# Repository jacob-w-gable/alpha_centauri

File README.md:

# Alpha Centauri KBD

This is a custom keyboard with a custom keymap that is specifically tailored to my hands and workflow style. It takes heavy inspiration from [crkbd v3](https://github.com/foostan/crkbd). The primary difference is the vertical spacing of the keys, and I have also removed one key from the outside column. The PCB is designed to support either MX or Choc v2 switches without sacrificing LED support. The keymap has been designed for comfort and efficiency, prioritizing typing/programming over other activities such as gaming.

### Assembled Choc Keyboard

### Assembled MX Keyboard

## Detailed Documentation

- [Quickstart](https://github.com/jacob-w-gable/alpha_centauri/wiki/Quickstart)
- [Designing/Fabricating the PCB](https://github.com/jacob-w-gable/alpha_centauri/wiki/Designing-and-Fabricating-PCB)
- TODO: PCB Assembly
- [Building/Flashing the Firmware](https://github.com/jacob-w-gable/alpha_centauri/wiki/Building-and-Flashing-Firmware)
- TODO: Printing the Case
- TODO: Final Assembly
- [Technical Layer Reference](https://github.com/jacob-w-gable/alpha_centauri/wiki/Technical-Layer-Reference)
- [Design Philosophy](https://github.com/jacob-w-gable/alpha_centauri/wiki/Design)

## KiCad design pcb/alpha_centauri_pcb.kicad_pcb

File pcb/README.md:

# PCB Files

These are the files required to edit the PCB in Kicad. One thing that makes this PCB stand out, is the fact that you can use hotswap sockets for either MX or Choc style switches, without compromising the ability to use per-key LEDs. While this does unfortunately cut off one of the pads, it does not make an electrical difference.

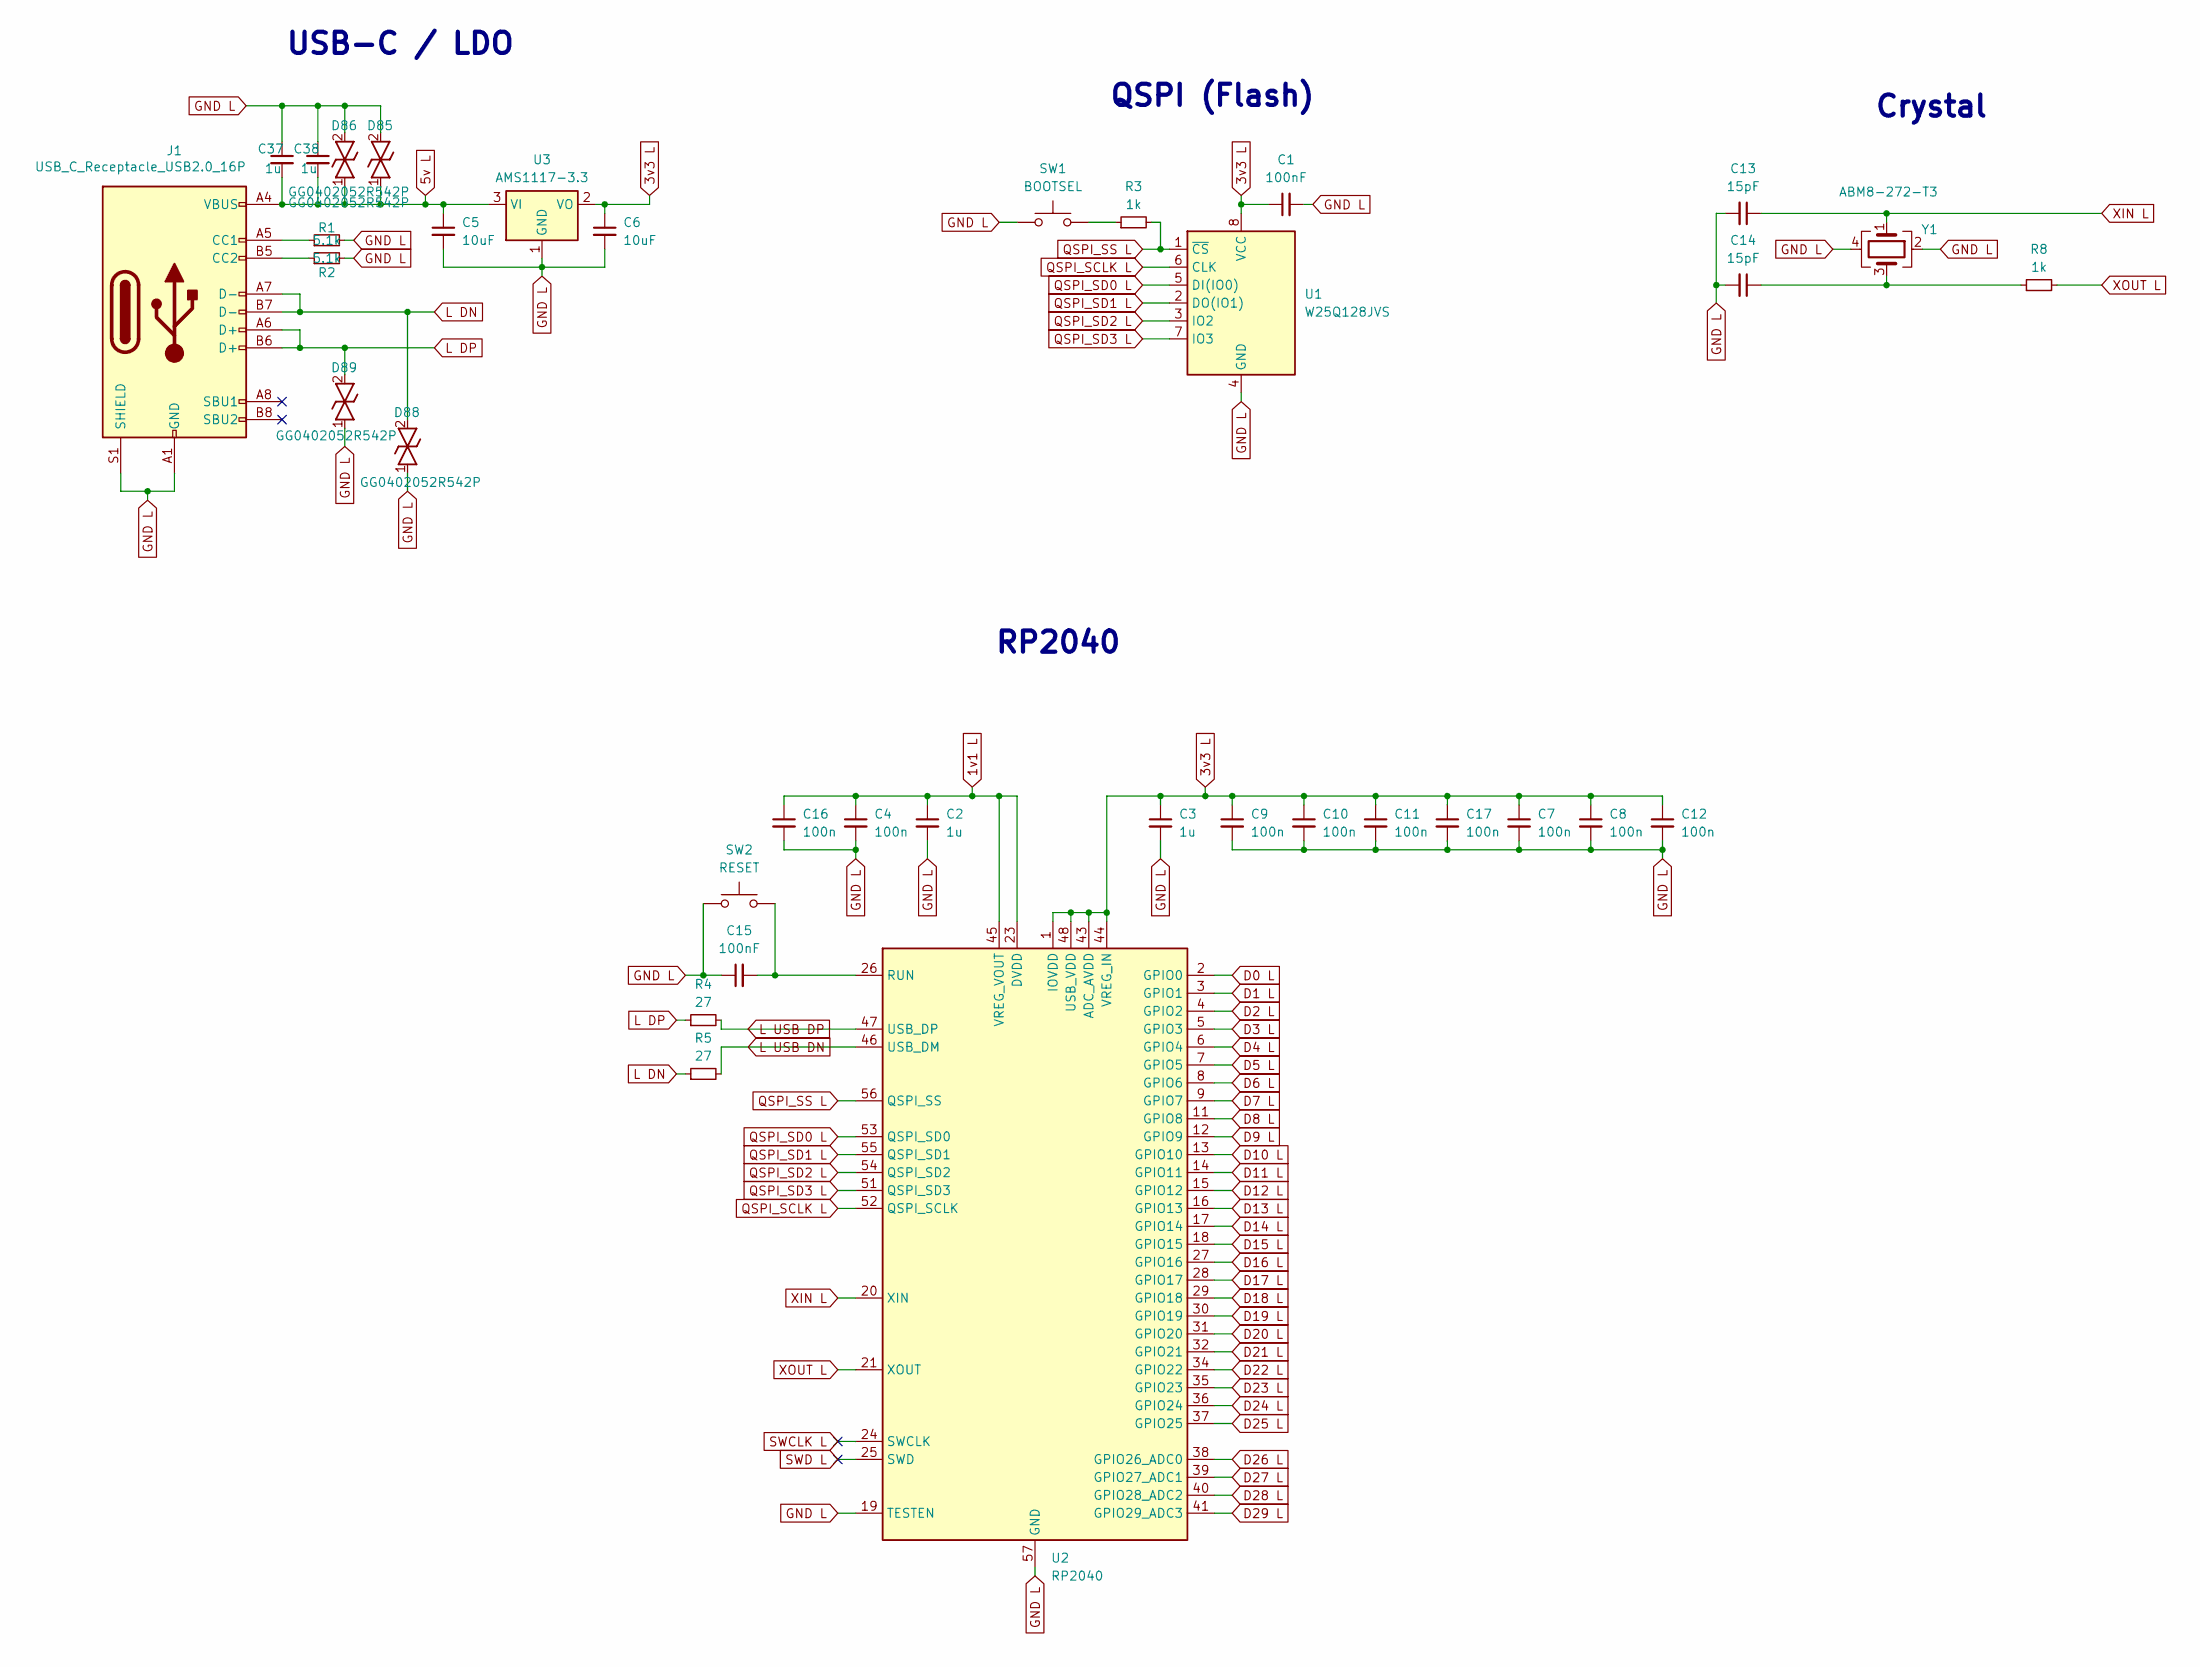
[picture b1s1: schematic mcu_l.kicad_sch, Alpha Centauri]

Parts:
C1, C15: 100nF; C_0603_1608Metric
C2, C3, C37, C38: 1u; C_0603_1608Metric
C4, C7, C8, C9, C10, C11, C12, C16, C17: 100n; C_0603_1608Metric
C5, C6: 10uF; C_0805_2012Metric
C13, C14: 15pF; C_0603_1608Metric
D85, D86, D88, D89: GG0402052R542P; DIONC1006X55N; Manufacturer_Part_Number GG0402052R542P; Mouser Part Number 581-GG0402052R542P
J1: USB_C_Receptacle_USB2.0_16P; USB_C_Receptacle_HRO_TYPE-C-31-M-12
R1, R2: 5.1k; R_0603_1608Metric
R3, R8: 1k; R_0603_1608Metric
R4, R5: 27; R_0603_1608Metric
SW1: BOOTSEL; EVQP2202M
SW2: RESET; EVQP2202M
U1: W25Q128JVS; SOIC127P790X216-8N
U2: RP2040; QFN-56-1EP_7x7mm_P0.4mm_EP3.2x3.2mm
U3: AMS1117-3.3; SOT-223-3_TabPin2
Y1: ABM8-272-T3; Crystal_SMD_3225-4Pin_3.2x2.5mm

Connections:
1v1 L: C2.1, C4.1, C16.1, U2.23 (DVDD), U2.45 (VREG_VOUT), U2.50 (DVDD)
3v3 L: C1.1, C3.1, C6.1, C7.1, C8.1, C9.1, C10.1, C11.1, C12.1, C17.1, U1.8 (VCC), U2.1 (IOVDD), U2.10 (IOVDD), U2.22 (IOVDD), U2.33 (IOVDD), U2.42 (IOVDD), U2.43 (ADC_AVDD), U2.44 (VREG_IN), U2.48 (USB_VDD), U2.49 (IOVDD), U3.2 (VO)
5v L: C5.1, C37.2, C38.2, D85.1, D86.1, J1.A4 (VBUS), J1.A9 (VBUS), J1.B4 (VBUS), J1.B9 (VBUS), U3.3 (VI); also elsewhere on the board
D0 L: U2.2 (GPIO0); also elsewhere on the board
D1 L: U2.3 (GPIO1)
D2 L: U2.4 (GPIO2)
D3 L: U2.5 (GPIO3)
D4 L: U2.6 (GPIO4); also elsewhere on the board
D5 L: U2.7 (GPIO5); also elsewhere on the board
D6 L: U2.8 (GPIO6); also elsewhere on the board
D7 L: U2.9 (GPIO7); also elsewhere on the board
D8 L: U2.11 (GPIO8); also elsewhere on the board
D9 L: U2.12 (GPIO9); also elsewhere on the board
D10 L: U2.13 (GPIO10)
D11 L: U2.14 (GPIO11)
D12 L: U2.15 (GPIO12)
D13 L: U2.16 (GPIO13)
D14 L: U2.17 (GPIO14)
D15 L: U2.18 (GPIO15)
D16 L: U2.27 (GPIO16)
D17 L: U2.28 (GPIO17)
D18 L: U2.29 (GPIO18)
D19 L: U2.30 (GPIO19)
D20 L: U2.31 (GPIO20); also elsewhere on the board
D21 L: U2.32 (GPIO21)
D22 L: U2.34 (GPIO22); also elsewhere on the board
D23 L: U2.35 (GPIO23)
D24 L: U2.36 (GPIO24)
D25 L: U2.37 (GPIO25)
D26 L: U2.38 (GPIO26_ADC0); also elsewhere on the board
D27 L: U2.39 (GPIO27_ADC1); also elsewhere on the board
D28 L: U2.40 (GPIO28_ADC2); also elsewhere on the board
D29 L: U2.41 (GPIO29_ADC3); also elsewhere on the board
GND L: C1.2, C2.2, C3.2, C4.2, C5.2, C6.2, C7.2, C8.2, C9.2, C10.2, C11.2, C12.2, C13.2, C14.2, C15.1, C16.2, C17.2, C37.1, C38.1, D85.2, D86.2, D88.1, D89.1, J1.A1 (GND), J1.A12 (GND), J1.B1 (GND), J1.B12 (GND), J1.S1 (SHIELD), R1.2, R2.2, SW1.1, SW2.1, U1.4 (GND), U2.19 (TESTEN), U2.57 (GND), U3.1 (GND), Y1.2, Y1.4; also elsewhere on the board
L DN: D88.2, J1.A7 (D-), J1.B7 (D-), R5.1
L DP: D89.2, J1.A6 (D+), J1.B6 (D+), R4.1
L USB DN: R5.2, U2.46 (USB_DM)
L USB DP: R4.2, U2.47 (USB_DP)
unnamed: C14.1, R8.1, Y1.3
unnamed: J1.A5 (CC1), R1.1
unnamed: J1.B5 (CC2), R2.1
unnamed: R3.1, SW1.2
unnamed: C15.2, SW2.2, U2.26 (RUN)
QSPI_SCLK L: U1.6 (CLK), U2.52 (QSPI_SCLK)
QSPI_SD0 L: U1.5 (DI(IO0)), U2.53 (QSPI_SD0)
QSPI_SD1 L: U1.2 (DO(IO1)), U2.55 (QSPI_SD1)
QSPI_SD2 L: U1.3 (IO2), U2.54 (QSPI_SD2)
QSPI_SD3 L: U1.7 (IO3), U2.51 (QSPI_SD3)
QSPI_SS L: R3.2, U1.1 (~CS), U2.56 (QSPI_SS)
SWCLK L: U2.24 (SWCLK)
SWD L: U2.25 (SWD)
XIN L: C13.1, U2.20 (XIN), Y1.1
XOUT L: R8.2, U2.21 (XOUT)

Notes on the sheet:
RP2040
QSPI (Flash)
USB-C / LDO
Crystal

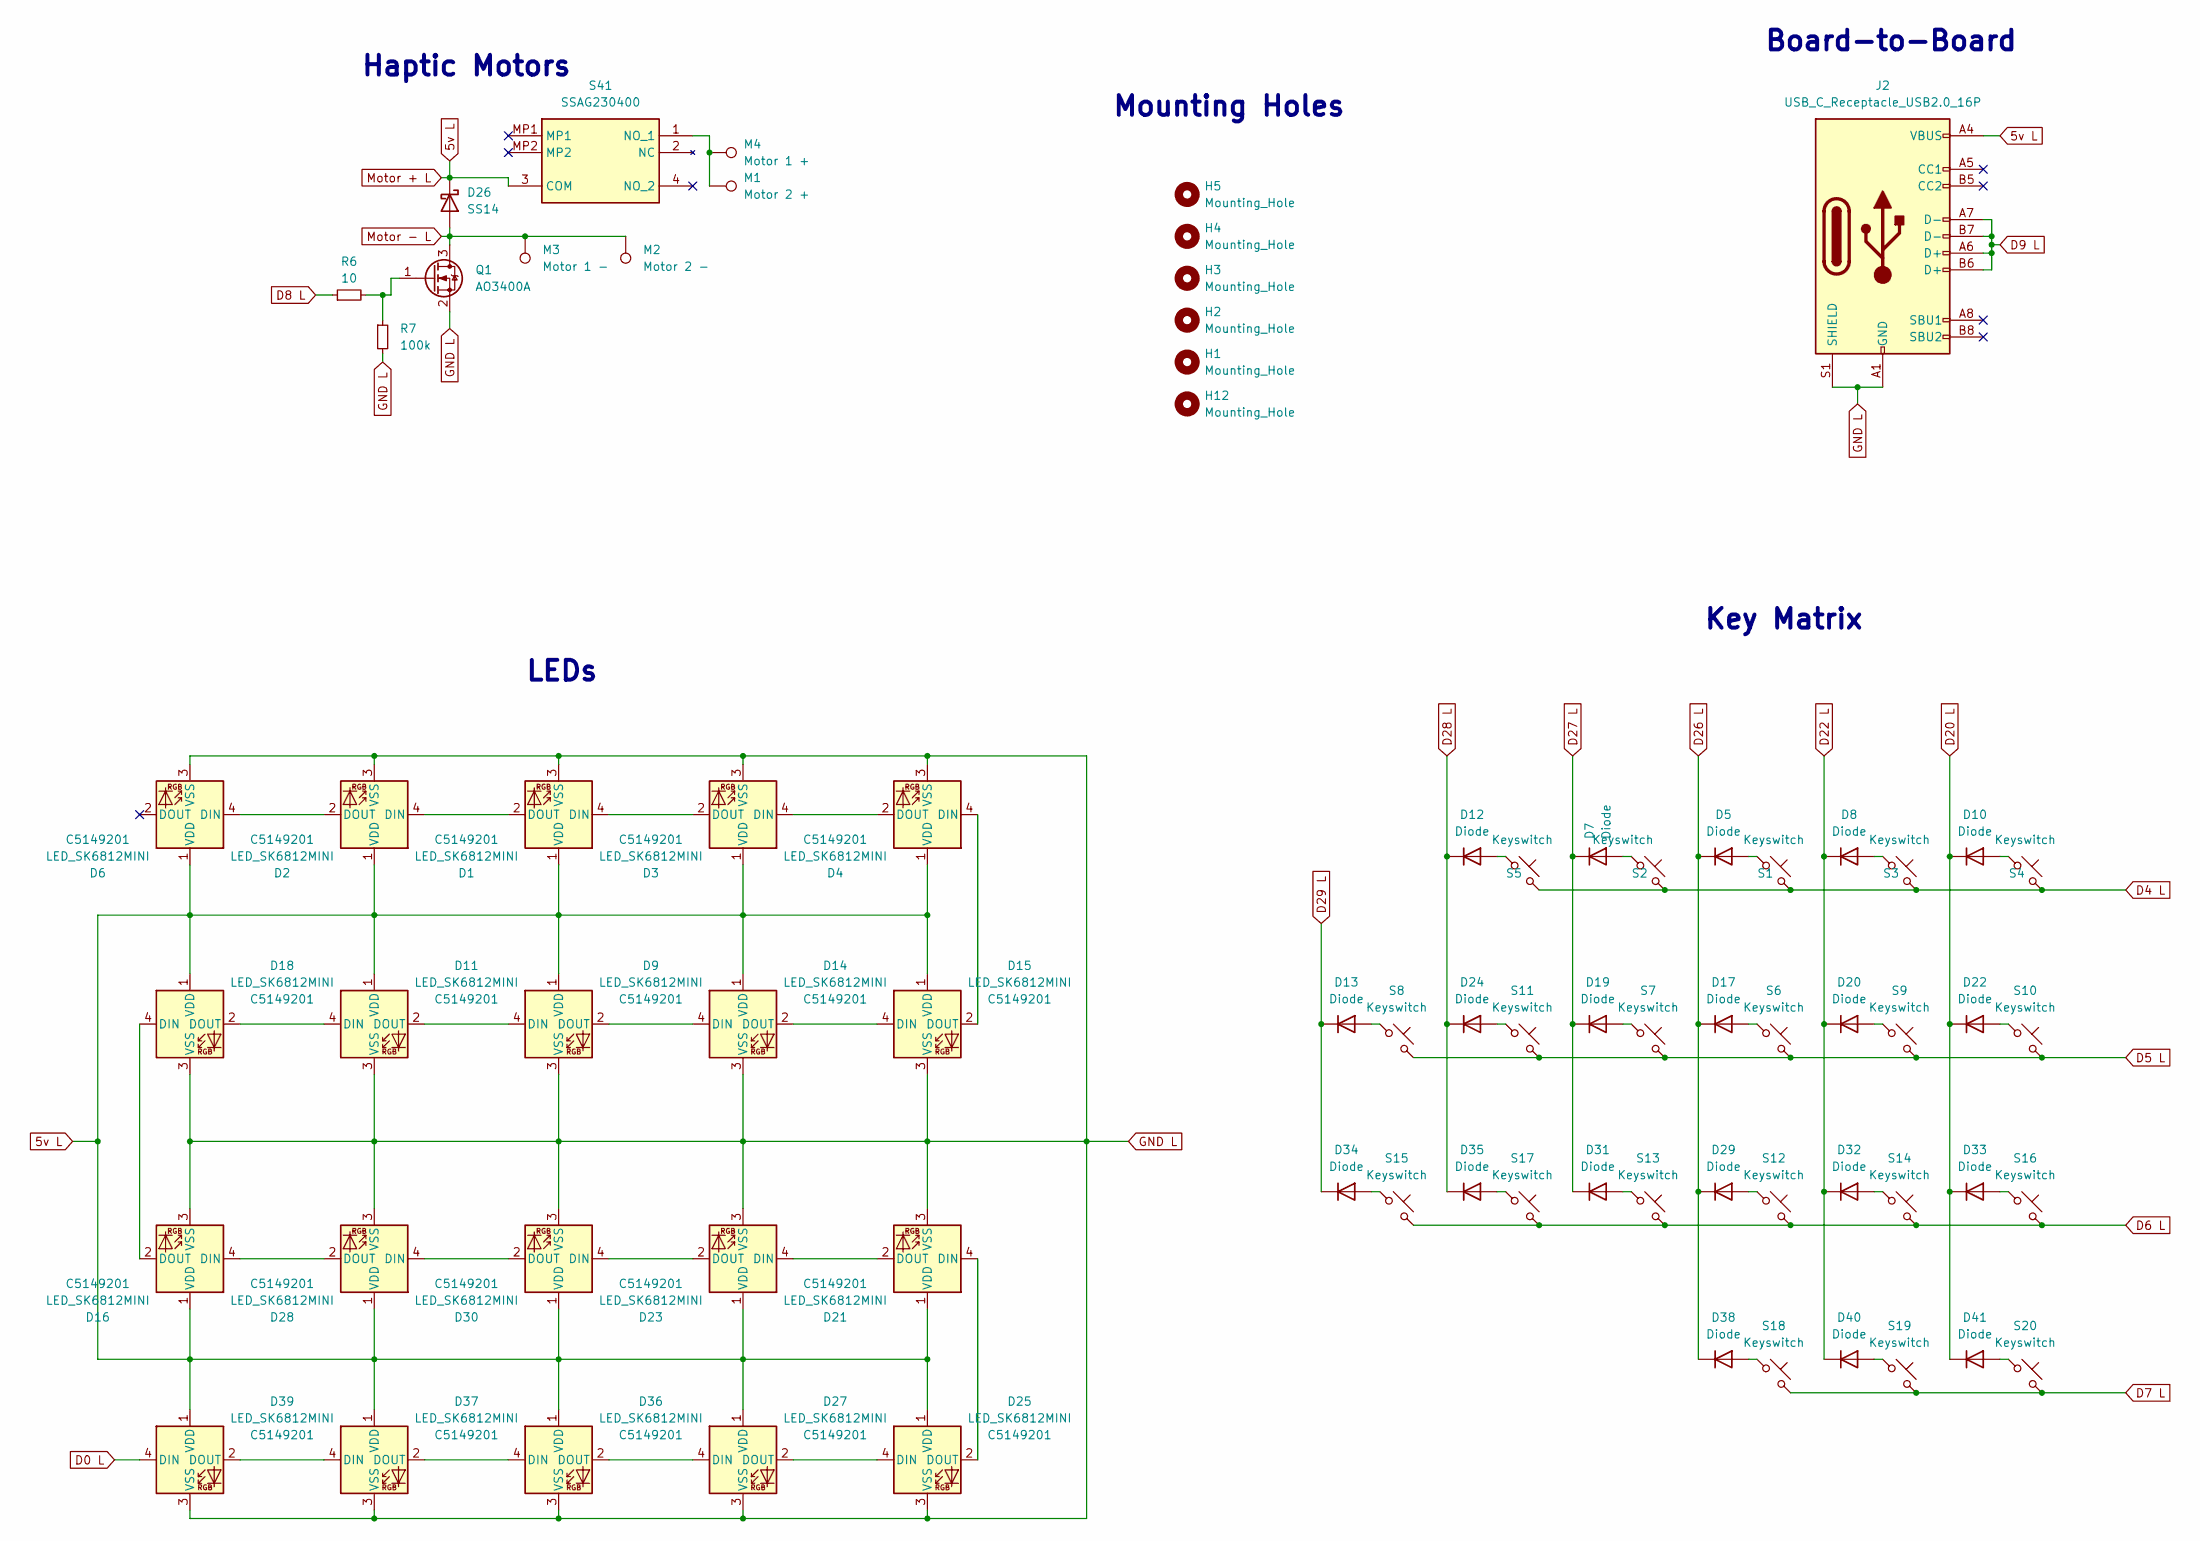
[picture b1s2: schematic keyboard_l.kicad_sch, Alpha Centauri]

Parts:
D1, D2, D3, D4, D6, D9, D11, D14, D15, D16, D18, D21, D23, D25, D27, D28, D30, D36, D37, D39: LED_SK6812MINI; LCSC C5149201
D5, D7, D8, D10, D12, D13, D17, D19, D20, D22, D24, D29, D31, D32, D33, D34, D35, D38, D40, D41: Diode; Diode_SOD-123
D26: SS14; D_SMA
H1, H2, H3, H4, H5, H12: Mounting_Hole; MountingHole_4.3mm_M4
J2: USB_C_Receptacle_USB2.0_16P; USB_C_Receptacle_HRO_TYPE-C-31-M-12
M1: Motor 2 +; TestPoint_Pad_2.5x2.5mm
M2: Motor 2 -; TestPoint_Pad_2.5x2.5mm
M3: Motor 1 -; TestPoint_Pad_2.5x2.5mm
M4: Motor 1 +; TestPoint_Pad_2.5x2.5mm
Q1: AO3400A; SOT-23
R6: 10; R_0603_1608Metric
R7: 100k; R_0603_1608Metric
S1, S2, S3, S4, S5, S6, S7, S9, S10, S11, S12, S13, S14, S15, S16, S17, S18, S19, S20: Keyswitch; MX_Choc_Hotswap_Hybrid
S8: Keyswitch; MX_Choc_Hotswap_Hybrid_1.5u
S41: SSAG230400; Manufacturer_Part_Number SSAG230400; Mouser Part Number 688-SSAG230400

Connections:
5v L: D1.1 (VDD), D2.1 (VDD), D3.1 (VDD), D4.1 (VDD), D6.1 (VDD), D9.1 (VDD), D11.1 (VDD), D14.1 (VDD), D15.1 (VDD), D16.1 (VDD), D18.1 (VDD), D21.1 (VDD), D23.1 (VDD), D25.1 (VDD), D26.1 (K), D27.1 (VDD), D28.1 (VDD), D30.1 (VDD), D36.1 (VDD), D37.1 (VDD), D39.1 (VDD), J2.A4 (VBUS), J2.A9 (VBUS), J2.B4 (VBUS), J2.B9 (VBUS), S41.3 (COM); also elsewhere on the board
D0 L: D39.4 (DIN); also elsewhere on the board
D4 L: S1.2, S2.2, S3.2, S4.2, S5.2; also elsewhere on the board
D5 L: S6.2, S7.2, S8.2, S9.2, S10.2, S11.2; also elsewhere on the board
D6 L: S12.2, S13.2, S14.2, S15.2, S16.2, S17.2; also elsewhere on the board
D7 L: S18.2, S19.2, S20.2; also elsewhere on the board
D8 L: R6.1; also elsewhere on the board
D9 L: J2.A6 (D+), J2.A7 (D-), J2.B6 (D+), J2.B7 (D-); also elsewhere on the board
D20 L: D10.1 (K), D22.1 (K), D33.1 (K), D41.1 (K); also elsewhere on the board
D22 L: D8.1 (K), D20.1 (K), D32.1 (K), D40.1 (K); also elsewhere on the board
D26 L: D5.1 (K), D17.1 (K), D29.1 (K), D38.1 (K); also elsewhere on the board
D27 L: D7.1 (K), D19.1 (K), D31.1 (K); also elsewhere on the board
D28 L: D12.1 (K), D24.1 (K), D35.1 (K); also elsewhere on the board
D29 L: D13.1 (K), D34.1 (K); also elsewhere on the board
GND L: D1.3 (VSS), D2.3 (VSS), D3.3 (VSS), D4.3 (VSS), D6.3 (VSS), D9.3 (VSS), D11.3 (VSS), D14.3 (VSS), D15.3 (VSS), D16.3 (VSS), D18.3 (VSS), D21.3 (VSS), D23.3 (VSS), D25.3 (VSS), D27.3 (VSS), D28.3 (VSS), D30.3 (VSS), D36.3 (VSS), D37.3 (VSS), D39.3 (VSS), J2.A1 (GND), J2.A12 (GND), J2.B1 (GND), J2.B12 (GND), J2.S1 (SHIELD), Q1.2 (S), R7.2; also elsewhere on the board
Motor - L: D26.2 (A), M2.1 (1_1), M3.1 (1_1), Q1.3 (D)
unnamed: D1.4 (DIN), D3.2 (DOUT)
unnamed: D1.2 (DOUT), D2.4 (DIN)
unnamed: D2.2 (DOUT), D6.4 (DIN)
unnamed: D3.4 (DIN), D4.2 (DOUT)
unnamed: D5.2 (A), S1.1
unnamed: D7.2 (A), S2.1
unnamed: D8.2 (A), S3.1
unnamed: D10.2 (A), S4.1
unnamed: D11.4 (DIN), D18.2 (DOUT)
unnamed: D9.4 (DIN), D11.2 (DOUT)
unnamed: D12.2 (A), S5.1
unnamed: D13.2 (A), S8.1
unnamed: D9.2 (DOUT), D14.4 (DIN)
unnamed: D14.2 (DOUT), D15.4 (DIN)
unnamed: D4.4 (DIN), D15.2 (DOUT)
unnamed: D16.4 (DIN), D28.2 (DOUT)
unnamed: D16.2 (DOUT), D18.4 (DIN)
unnamed: D17.2 (A), S6.1
unnamed: D19.2 (A), S7.1
unnamed: D20.2 (A), S9.1
unnamed: D21.4 (DIN), D25.2 (DOUT)
unnamed: D21.2 (DOUT), D23.4 (DIN)
unnamed: D22.2 (A), S10.1
unnamed: D23.2 (DOUT), D30.4 (DIN)
unnamed: D24.2 (A), S11.1
unnamed: D25.4 (DIN), D27.2 (DOUT)
unnamed: D27.4 (DIN), D36.2 (DOUT)
unnamed: D28.4 (DIN), D30.2 (DOUT)
unnamed: D29.2 (A), S12.1
unnamed: D31.2 (A), S13.1
unnamed: D32.2 (A), S14.1
unnamed: D33.2 (A), S16.1
unnamed: D34.2 (A), S15.1
unnamed: D35.2 (A), S17.1
unnamed: D36.4 (DIN), D37.2 (DOUT)
unnamed: D37.4 (DIN), D39.2 (DOUT)
unnamed: D38.2 (A), S18.1
unnamed: D40.2 (A), S19.1
unnamed: D41.2 (A), S20.1
unnamed: Q1.1 (G), R6.2, R7.1
unnamed: M1.1 (1_1), M4.1 (1_1), S41.1 (NO_1)

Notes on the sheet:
Board-to-Board
Haptic Motors
Key Matrix
LEDs
Mounting Holes

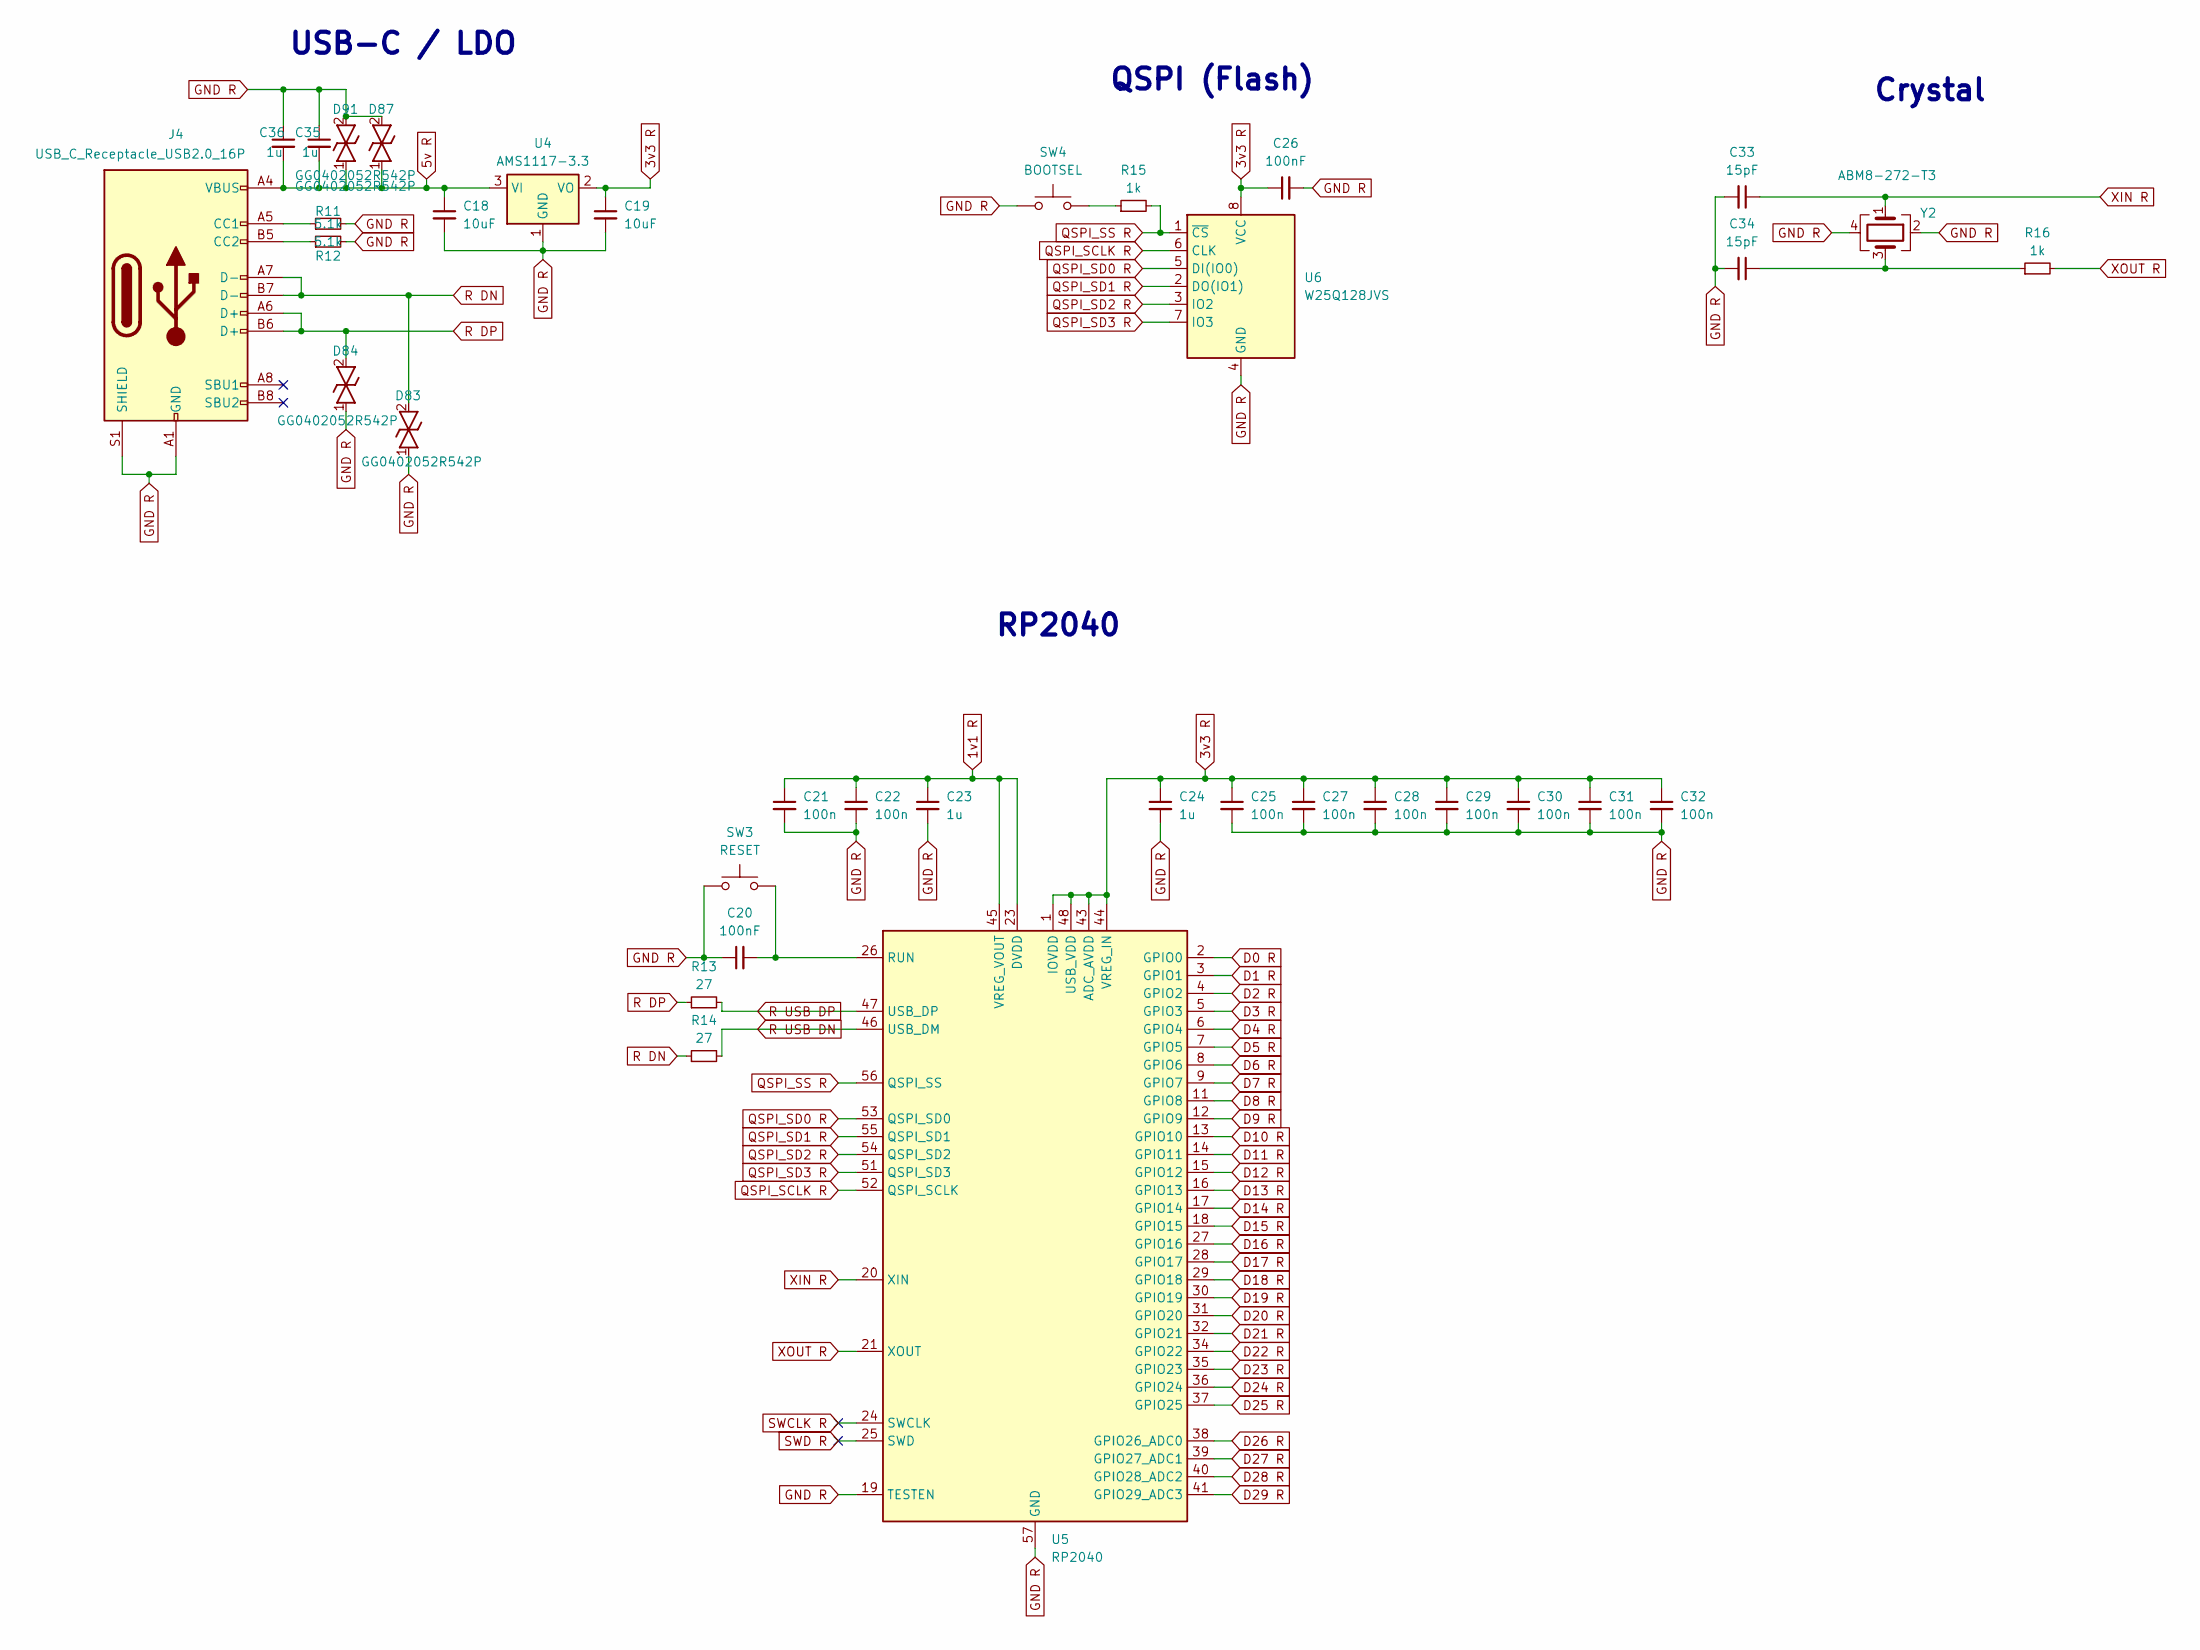
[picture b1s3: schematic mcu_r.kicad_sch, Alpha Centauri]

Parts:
C18, C19: 10uF; C_0805_2012Metric
C20, C26: 100nF; C_0603_1608Metric
C21, C22, C25, C27, C28, C29, C30, C31, C32: 100n; C_0603_1608Metric
C23, C24, C35, C36: 1u; C_0603_1608Metric
C33, C34: 15pF; C_0603_1608Metric
D83, D84, D87, D91: GG0402052R542P; DIONC1006X55N; Manufacturer_Part_Number GG0402052R542P; Mouser Part Number 581-GG0402052R542P
J4: USB_C_Receptacle_USB2.0_16P; USB_C_Receptacle_HRO_TYPE-C-31-M-12
R11, R12: 5.1k; R_0603_1608Metric
R13, R14: 27; R_0603_1608Metric
R15, R16: 1k; R_0603_1608Metric
SW3: RESET; EVQP2202M
SW4: BOOTSEL; EVQP2202M
U4: AMS1117-3.3; SOT-223-3_TabPin2
U5: RP2040; QFN-56-1EP_7x7mm_P0.4mm_EP3.2x3.2mm
U6: W25Q128JVS; SOIC127P790X216-8N
Y2: ABM8-272-T3; Crystal_SMD_3225-4Pin_3.2x2.5mm

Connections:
1v1 R: C21.1, C22.1, C23.1, U5.23 (DVDD), U5.45 (VREG_VOUT), U5.50 (DVDD)
3v3 R: C19.1, C24.1, C25.1, C26.1, C27.1, C28.1, C29.1, C30.1, C31.1, C32.1, U4.2 (VO), U5.1 (IOVDD), U5.10 (IOVDD), U5.22 (IOVDD), U5.33 (IOVDD), U5.42 (IOVDD), U5.43 (ADC_AVDD), U5.44 (VREG_IN), U5.48 (USB_VDD), U5.49 (IOVDD), U6.8 (VCC)
5v R: C18.1, C35.2, C36.2, D87.1, D91.1, J4.A4 (VBUS), J4.A9 (VBUS), J4.B4 (VBUS), J4.B9 (VBUS), U4.3 (VI); also elsewhere on the board
D0 R: U5.2 (GPIO0); also elsewhere on the board
D1 R: U5.3 (GPIO1)
D2 R: U5.4 (GPIO2)
D3 R: U5.5 (GPIO3)
D4 R: U5.6 (GPIO4); also elsewhere on the board
D5 R: U5.7 (GPIO5); also elsewhere on the board
D6 R: U5.8 (GPIO6); also elsewhere on the board
D7 R: U5.9 (GPIO7); also elsewhere on the board
D8 R: U5.11 (GPIO8); also elsewhere on the board
D9 R: U5.12 (GPIO9); also elsewhere on the board
D10 R: U5.13 (GPIO10)
D11 R: U5.14 (GPIO11)
D12 R: U5.15 (GPIO12)
D13 R: U5.16 (GPIO13)
D14 R: U5.17 (GPIO14)
D15 R: U5.18 (GPIO15)
D16 R: U5.27 (GPIO16)
D17 R: U5.28 (GPIO17)
D18 R: U5.29 (GPIO18)
D19 R: U5.30 (GPIO19)
D20 R: U5.31 (GPIO20); also elsewhere on the board
D21 R: U5.32 (GPIO21)
D22 R: U5.34 (GPIO22); also elsewhere on the board
D23 R: U5.35 (GPIO23)
D24 R: U5.36 (GPIO24)
D25 R: U5.37 (GPIO25)
D26 R: U5.38 (GPIO26_ADC0); also elsewhere on the board
D27 R: U5.39 (GPIO27_ADC1); also elsewhere on the board
D28 R: U5.40 (GPIO28_ADC2); also elsewhere on the board
D29 R: U5.41 (GPIO29_ADC3); also elsewhere on the board
GND R: C18.2, C19.2, C20.1, C21.2, C22.2, C23.2, C24.2, C25.2, C26.2, C27.2, C28.2, C29.2, C30.2, C31.2, C32.2, C33.2, C34.2, C35.1, C36.1, D83.1, D84.1, D87.2, D91.2, J4.A1 (GND), J4.A12 (GND), J4.B1 (GND), J4.B12 (GND), J4.S1 (SHIELD), R11.2, R12.2, SW3.1, SW4.1, U4.1 (GND), U5.19 (TESTEN), U5.57 (GND), U6.4 (GND), Y2.2, Y2.4; also elsewhere on the board
unnamed: C34.1, R16.1, Y2.3
unnamed: J4.A5 (CC1), R11.1
unnamed: J4.B5 (CC2), R12.1
unnamed: R15.1, SW4.2
unnamed: C20.2, SW3.2, U5.26 (RUN)
QSPI_SCLK R: U5.52 (QSPI_SCLK), U6.6 (CLK)
QSPI_SD0 R: U5.53 (QSPI_SD0), U6.5 (DI(IO0))
QSPI_SD1 R: U5.55 (QSPI_SD1), U6.2 (DO(IO1))
QSPI_SD2 R: U5.54 (QSPI_SD2), U6.3 (IO2)
QSPI_SD3 R: U5.51 (QSPI_SD3), U6.7 (IO3)
QSPI_SS R: R15.2, U5.56 (QSPI_SS), U6.1 (~CS)
R DN: D83.2, J4.A7 (D-), J4.B7 (D-), R14.1
R DP: D84.2, J4.A6 (D+), J4.B6 (D+), R13.1
R USB DN: R14.2, U5.46 (USB_DM)
R USB DP: R13.2, U5.47 (USB_DP)
SWCLK R: U5.24 (SWCLK)
SWD R: U5.25 (SWD)
XIN R: C33.1, U5.20 (XIN), Y2.1
XOUT R: R16.2, U5.21 (XOUT)

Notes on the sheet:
RP2040
QSPI (Flash)
Crystal
USB-C / LDO
